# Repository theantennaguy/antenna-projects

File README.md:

# antenna-projects
This repository contains board files and/or mechanical files of antennas I showcase on my blog. Info can also be found in the 'documentation' folder of each antenna.

All board/mechanical designs in this repository are licensed under CERN-OHL-S v2. You can check the license file located at the base of the repository. It can also be found here https://ohwr.org/cern_ohl_s_v2.txt.

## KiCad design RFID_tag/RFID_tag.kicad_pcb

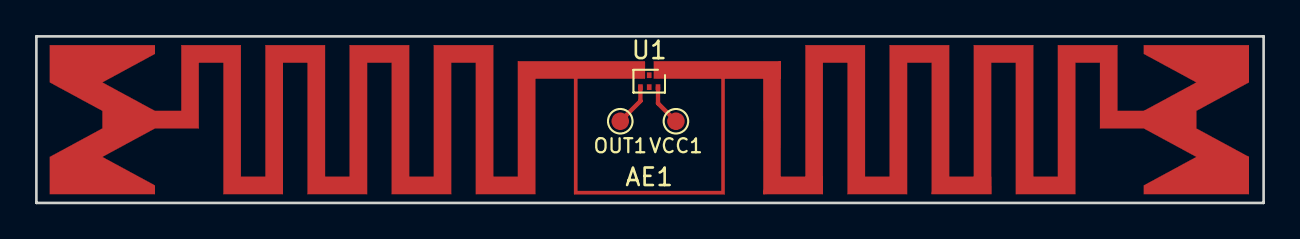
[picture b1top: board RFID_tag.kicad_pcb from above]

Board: 2 copper layers, 70.0 x 9.5 mm, 4 parts (0 on the bottom side), 4 nets.

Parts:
AE1: Antenna_Dipole; RFID_tag_915MHz_NXP_UCODE_G2IM+
OUT1: TestPoint; TestPoint_Pad_D1.0mm
U1: SL3S1013FTB0; SOT-886
VCC1: TestPoint; TestPoint_Pad_D1.0mm

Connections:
unnamed: AE1.1, U1.3
unnamed: AE1.2, U1.1
unnamed: OUT1.1, U1.4
unnamed: U1.6, VCC1.1

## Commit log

2021-03-08 Create License
2021-03-08 Update repository 2021/03/08
2021-03-11 update quadrifilar_antenna boards A and B
2021-03-24 - added quadrifilar part C and mech assembly
2021-03-24 - minor corrections to quadrifilar section A
2021-03-28 Minor update to part A

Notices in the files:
RFID_tag/RFID_tag.kicad_pcb:
Copyright (C) 2021 Ricardo Goncalves
